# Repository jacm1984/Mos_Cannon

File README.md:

# Mos_Cannon
PCB Design for ground release adapter

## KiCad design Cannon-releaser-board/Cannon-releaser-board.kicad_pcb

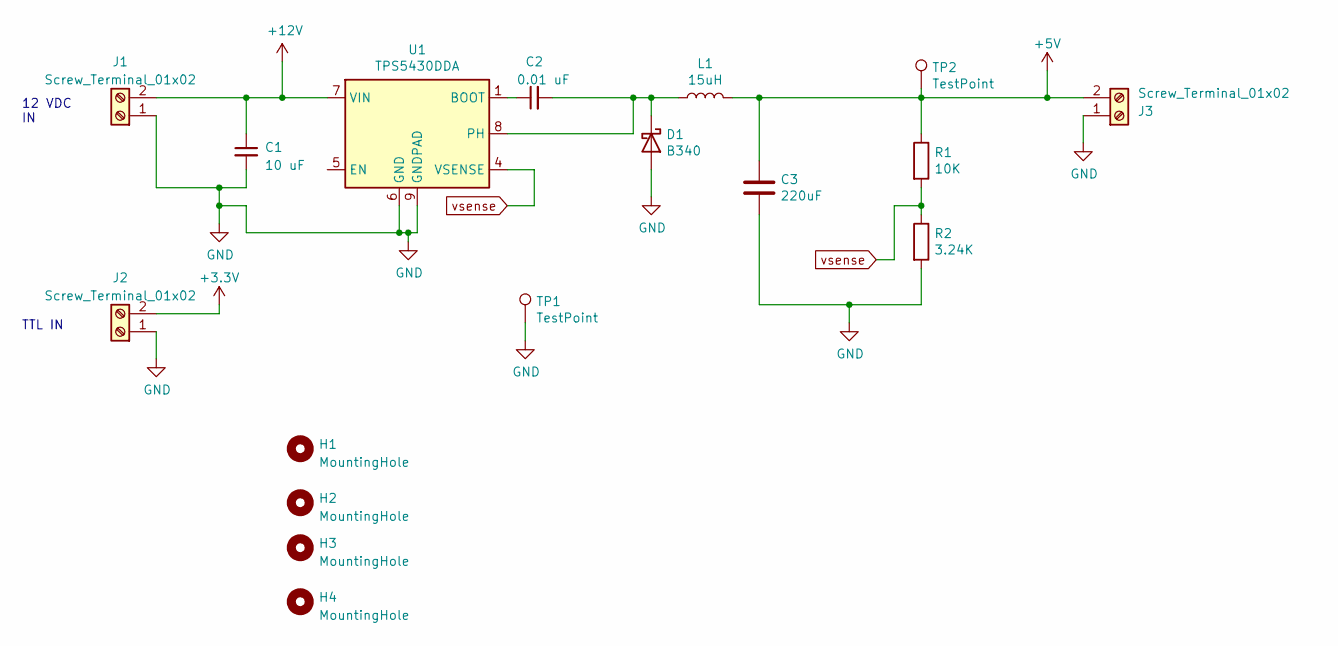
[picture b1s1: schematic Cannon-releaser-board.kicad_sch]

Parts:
C1: 10 uF; C_0805_2012Metric; Digi-Key Part # 1276-6454-2-ND
C2: 0.01 uF; C_0603_1608Metric; Digi-Key Part # 1292-1405-2-ND
C3: 220uF; CP_EIA-7343-15_Kemet-W_Pad2.25x2.55mm_HandSolder; Digi-Key Part # P16447TR-ND
D1: B340; D_SMA; JLCPCB Part # C64982
H1, H2, H3, H4: MountingHole; MountingHole_2.5mm
J1, J2, J3: Screw_Terminal_01x02; TerminalBlock_Phoenix_MKDS-1,5-2-5.08_1x02_P5.08mm_Horizont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; JLCPCB Part # C91153
L1: 15uH; L_10.4x10.4_H4.8; Digi-Key Part # 308-2278-2-ND
R1: 10K; R_0402_1005Metric; Digi-Key Part # 311-10KJRTR-ND
R2: 3.24K; R_0402_1005Metric; Digi-Key Part # YAG3147TR-ND
TP1, TP2: TestPoint; TestPoint_Pad_2.0x2.0mm
U1: TPS5430DDA; TI_SO-PowerPAD-8_ThermalVias; JLCPCB Part # C9864

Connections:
+3.3V: J2.2
+5V: C3.1, J3.2, L1.2, R1.1, TP2.1
+12V: C1.1, J1.2, U1.7 (VIN)
GND: C1.2, C3.2, D1.2 (A), J1.1, J2.1, J3.1, R2.2, TP1.1, U1.6 (GND), U1.9 (GNDPAD)
unnamed: C2.2, D1.1 (K), L1.1, U1.8 (PH)
unnamed: C2.1, U1.1 (BOOT)
vsense: R1.2, R2.1, U1.4 (VSENSE)

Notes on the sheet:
12 VDC IN
TTL IN

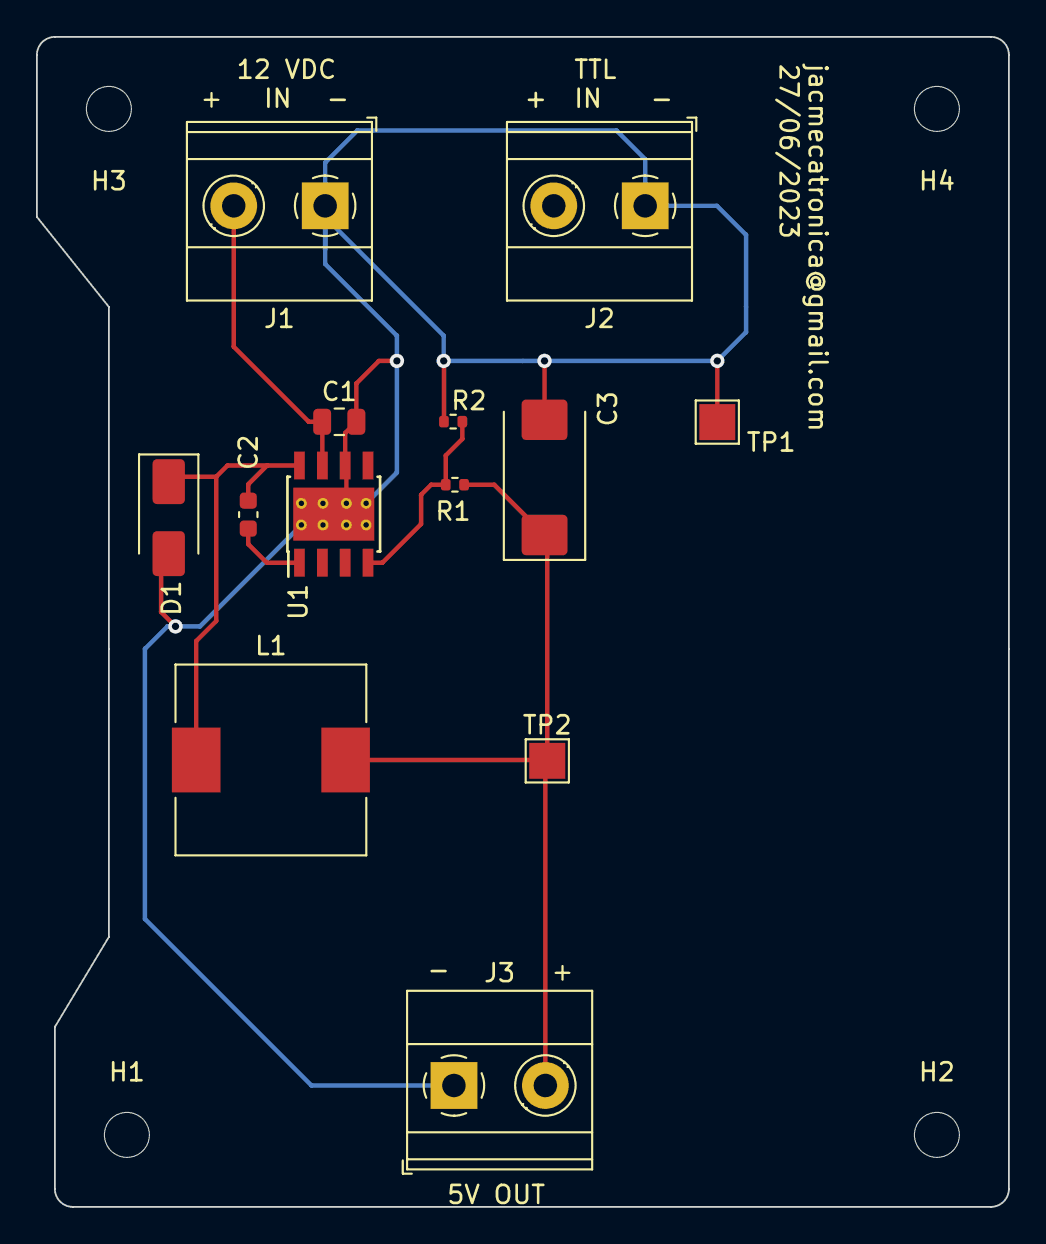
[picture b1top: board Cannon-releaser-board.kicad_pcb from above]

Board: 2 copper layers, 54.0 x 65.0 mm, 17 parts (0 on the bottom side), 6 nets.

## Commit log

2023-07-01 Mosquito Cannon board
